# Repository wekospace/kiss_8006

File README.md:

Repository content
==================

 * datasheets

Datasheets of chips on front panel.

 * front-panel

Schematics and sniffing traces of front panel.

 * pikmm

Schematic and PCB for Raspberry Pi to Kmm front panel interface.

 * pyk8006

Python files (modules, tests, examples) to drive Kmm front panel.

Devices
=======

During development, a K8006 device have been used but this product does exist under various names :
 * KMM3010-SC-B
 * K8006
 * Media Receiver 300
 * X300T
 * KISS KMM
 * Bluewin TV-Box
 * VIP 1216

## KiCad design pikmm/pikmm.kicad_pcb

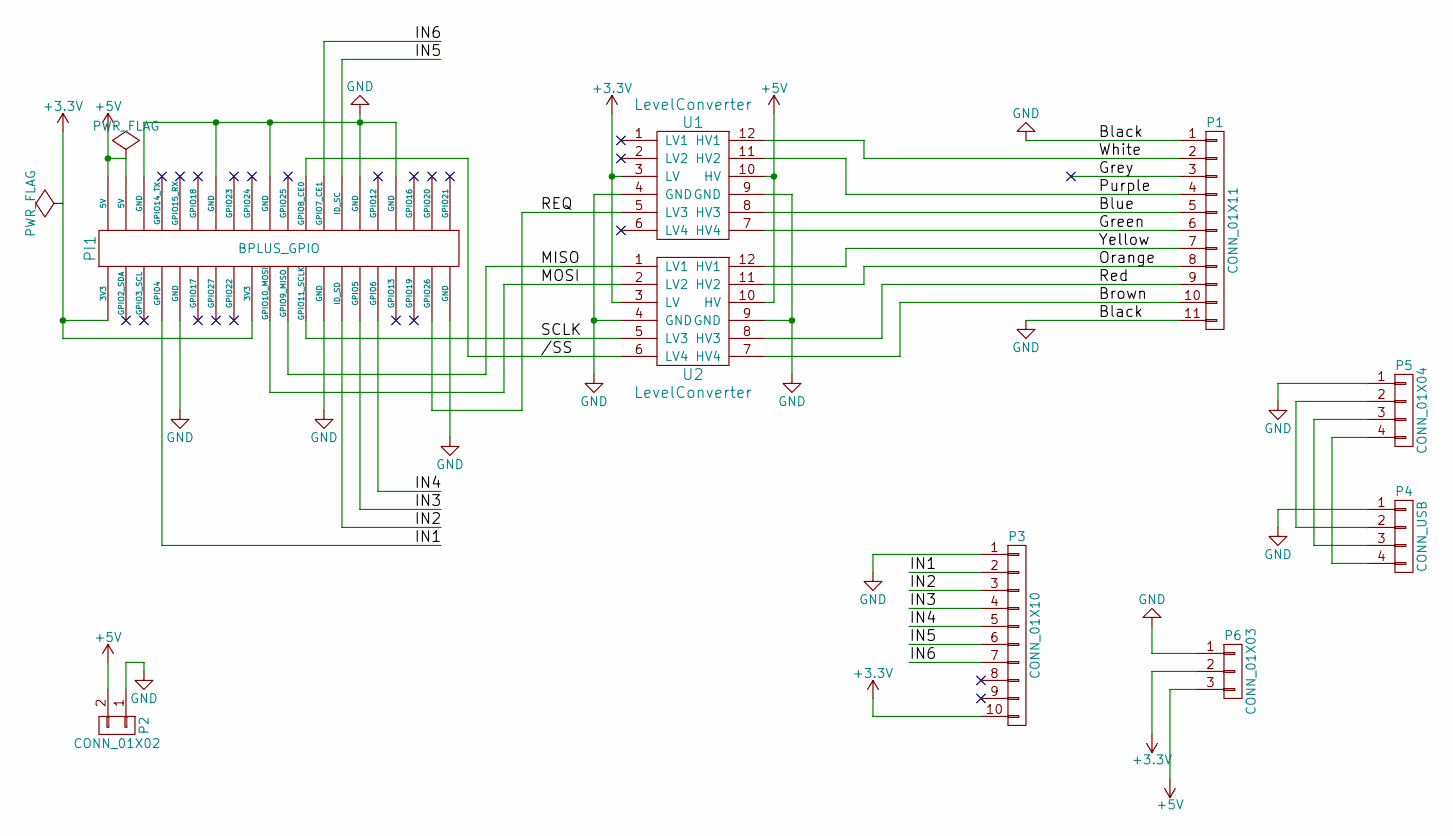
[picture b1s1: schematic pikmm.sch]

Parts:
P1: CONN_01X11; Molex_PicoBlade_53047-1110
P2: CONN_01X02; Pin_Header_Straight_1x02
P3: CONN_01X10; Pin_Header_Straight_1x10
P4: CONN_USB; Pin_Header_Straight_1x04_Pitch2.00mm
P5: CONN_01X04; Pin_Header_Straight_1x04
P6: CONN_01X03; Pin_Header_Straight_1x03
PI1: BPLUS_GPIO; Pin_Header_Straight_2x20
U1, U2: LevelConverter; DIP12_W5

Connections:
+3V3: P3.10, P6.2, PI1.1 (3V3), PI1.17 (3V3), U1.3 (LV), U2.3 (LV)
+5V: P2.2, P6.3, PI1.2 (5V), PI1.4 (5V), U1.10 (HV), U2.10 (HV)
//SS: PI1.24 (GPIO8_CE0), U2.6 (LV4)
/Blue: P1.5, U1.8 (HV3)
/Brown: P1.10, U2.7 (HV4)
/Green: P1.6, U1.7 (HV4)
/Grey: P1.3
/IN1: P3.2, PI1.7 (GPIO4)
/IN2: P3.3, PI1.27 (ID_SD)
/IN3: P3.4, PI1.29 (GPIO5)
/IN4: P3.5, PI1.31 (GPIO6)
/IN5: P3.6, PI1.28 (ID_SC)
/IN6: P3.7, PI1.26 (GPIO7_CE1)
/MISO: PI1.21 (GPIO9_MISO), U2.1 (LV1)
/MOSI: PI1.19 (GPIO10_MOSI), U2.2 (LV2)
/Orange: P1.8, U2.11 (HV2)
/Purple: P1.4, U1.11 (HV2)
/REQ: PI1.37 (GPIO26), U1.5 (LV3)
/Red: P1.9, U2.8 (HV3)
/SCLK: PI1.23 (GPIO11_SCLK), U2.5 (LV3)
/White: P1.2, U1.12 (HV1)
/Yellow: P1.7, U2.12 (HV1)
GND: P1.1, P1.11, P2.1, P3.1, P4.1, P5.1, P6.1, PI1.6 (GND), PI1.9 (GND), PI1.14 (GND), PI1.20 (GND), PI1.25 (GND), PI1.30 (GND), PI1.34 (GND), PI1.39 (GND), U1.4 (GND), U1.9 (GND), U2.4 (GND), U2.9 (GND)
unnamed: P4.2, P5.2
unnamed: P4.3, P5.3
unnamed: P4.4, P5.4

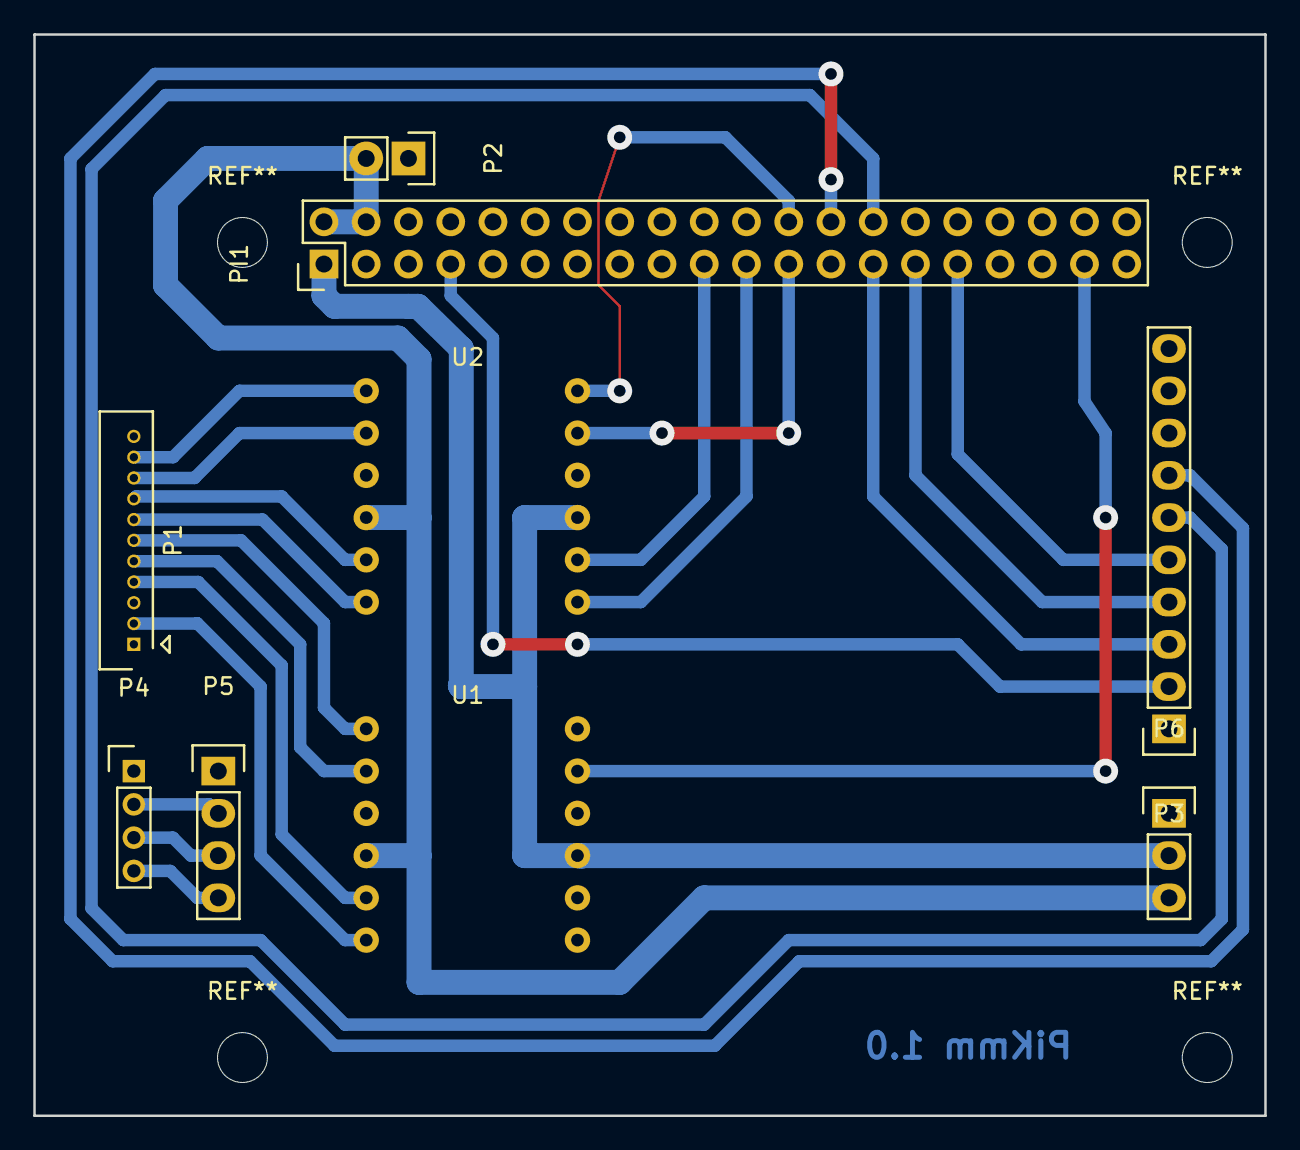
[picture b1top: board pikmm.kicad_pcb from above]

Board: 2 copper layers, 74.0 x 65.0 mm, 9 parts (0 on the bottom side), 25 nets.

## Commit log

2015-11-28 Import front panel schema
2016-01-17 Initial import of pyk8006
    A tool to drive front panel of k8006
2016-01-17 Import decoded frames and fuzzing results
2016-01-17 Move schematics into dedicated directory
2016-01-17 Import sigrok session of initialization
2016-01-17 Commit as backup, sorry for dirty things ;)
2016-01-24 Rework python module
    * Add tests
    * Rename functions
    * Use python3
    * Introduice new discovered commands (and features)
2016-02-05 Minor clean up
2016-02-05 Remove unused function
2016-02-05 Attempt to be more PEP8 :)
2016-02-06 PEP8: python3's default encoding is UTF-8
2016-02-06 Implement an async io thread.
    This commit allow to choose to use a thread to handle IO with Kmm (K8006 front-panel).
    Threading this task permit full-duplex communication: ie. being able to send commands while receiving data.
    Additionnally, this now allow multiple task to queue commands to front panel and to prevent from loosing incomming data
2016-02-06 "k8006" module is now "kmm" package
2016-02-06 Split sources into dedicated files and rename to Kmm*
2016-02-06 Remove old files
2016-02-06 Move LedColor Enum to bottom of file
2016-02-06 Add IR keys mapping.
    This commit also introduces input_button callback
2016-02-06 Buttons test: only display debug when debug is enabled
2016-02-06 Fix "voicemail" IR remote key name
2016-02-06 Add KmmPi class to ease setup on Raspberry Pi
2016-02-07 Move request_reception() function before register_input_button_callback()
2016-02-07 Rework input event handling
    Add a dedicated decoder class.
    Detect pressed and hold keys and report them as it with timestamp and duration when relevant (ie. hold)
2016-02-07 test_pi_buttons.py: minor fix
2016-02-07 Test input event duration using VFD
2016-02-08 KmmPi: fix debug flag
2016-02-08 KmmInputEvent: handle Ir key released
2016-02-08 Implement front panel button as KmmInputEvent (pressed, hold and released)
2016-04-08 Schematic: renamed SPI wires
2016-04-09 PiKmm: initial import
2016-05-08 test_pi_buttons: make it works with PiKmm board
2016-05-08 test_pi_buttons: count detected failures
    Note: it could have false-positive failures due to unsynchronized thread
2016-06-10 Add universal remote guide (in french)
2016-06-10 Tests: add raw Pi IRQ pin test
2016-06-10 Import xbmcclient.py from https://github.com/xbmc/xbmc
    The file have been fetched using:
    wget https://raw.githubusercontent.com/xbmc/xbmc/master/tools/EventClients/lib/python/xbmcclient.py
    (git commit: b0fa5b3d3209a55c4f7742026d8fc51df8fc8b93)
2016-06-10 XBMCClient: use python 3
2016-06-10 pyk8006: set IRQ default pin to PiKmm IRQ pin
2016-06-10 Kodi remote: import kodi client to handle Kmm buttons (local and remote)
2016-06-10 XBMCClient: remove debug-related prints
2016-06-10 Add a README
2016-06-13 Kodiremote: set power LED to green
2016-06-13 Kodiremote: use it as a user service (systemd)
2016-06-13 tests: load module from path relative to script location
2016-06-13 test_pi_buttons: remove junk code
2016-06-13 Kmm: rework IR inputs handling
2016-06-13 KmmIoThread: resync received frame on start byte when relevant
    This commit allow to sync to start of frame when:
    * We receive bytes after start byte (e.g. after a crash)
    * We receive a frame which contains another 0x23, which means we have a bad frame
2016-06-17 Kmm: do not crash when key is badly received
2016-06-17 Kmm: improve print-based debug
2016-06-17 Kmm: only drop frame if current frame is corrupt, not whole buffer
2016-06-17 KmmInputEvent: release last button on error
2016-06-18 Relay: import RelayBoard module
2016-06-18 Kmm: do not check callback if not relevant
2016-06-18 Kmm: add a input event worker
2016-06-18 Kmm: put some notes on reversed commands
2016-06-18 Rename pyk8006 into python
2016-06-18 Move relay test into tests/
2016-06-18 KissMPD: import new module for MPD
2016-06-18 KissMeD: import main kissme daemon
2016-06-18 KissMPD: display track duration
2016-06-18 KissMPD: fix previous()
2016-06-18 Kodiremote: rename python script
2016-06-18 KissMeD: allow to load module from ../share/pyshared/
2016-06-18 KissMeD: center text when display current mode
2016-06-18 KissMeD: minor text displaying fixes
2016-06-18 KissMeD: use dict to assign functions to keys
2016-06-18 KissMPD: return state change on update_status()
2016-06-18 KissMPD: fix volume limits
2016-06-18 KissMPD: implement missing pause() and play_pause()
2016-06-18 KissMeD: power on when music is started when KissMe is off
2016-06-18 KissMeD: put operations in a KissMe class
2016-06-18 KissMPD: do not print change on stdout
2016-06-18 KissMPD: display state change on VFD
2016-06-18 Kmm: clear() now really clear VFD (not only text)
2016-06-18 KimInputEventWorker: do not catch bugs :)
2016-06-18 KissMeD: add a systemd service unit
2016-06-18 Kmm: add a tiny tool to test directly commands and raw data
2016-06-19 KissMeD service: improve output to journalctl
2016-06-19 KissMeD: auto-shutdown when unused
2016-06-19 KissMeD: let "Video" display on video mode
2016-06-19 KissMPD: pause() should not un-pause
2016-06-19 Kmm: truncate payload to max lenght
2016-06-19 KissMeD: handle music-realated keys in KissMPD module
2016-06-19 Convert KodiClient daemon into module 1/2
2016-06-19 Convert KodiClient daemon into module 2/2
2016-06-19 KissMeD: use KissKodi for video mode
2016-06-19 KissMeD: stop video when leaving video mode
2016-07-04 KissMed: sync multi-thread reading of "mode"
2016-07-04 Relay: handle amplifier relay
2016-07-04 KissKodi: support volume up/down key holding
2016-07-04 KissMed: raise to 5min the time before shutting down
2016-07-04 KissMPD: fix text when track have no title or artist
2016-07-06 KissMPD: do not display time when tag is not available
2016-11-11 Update schematics
2016-11-11 Import case drawings and milling stand
2017-02-25 KissMeD: enable luz power control
2017-03-21 Relay: support "1" as True
2017-03-21 KissMeD: assign yellow key to console mode
2017-03-26 KissKodi: display action using "flashing text"
2017-03-26 KissMeD: reduce hold time to switch mode
2017-03-26 KissMPD: display some blanks between text scrolls
2017-03-26 KissMeD: refresh display using mode string when not defined
2017-10-01 PiKmm: fixes submodules usage
